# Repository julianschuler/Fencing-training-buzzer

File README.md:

# Fencing training buzzer
## Overview
This repository contains the schematic and PCB files for training buzzer circuits for sport fencing. These devices are intended to be attached directly to the plug of a foil respectively epee and will beep and flash a LED for a short period of time if a hit is detected. The buzzer circuits are powered by 1F 5.5V supercapacitors and thus can be recharged quickly by connecting them to a 5V wall adapter (less than 150 seconds for a full charge). The weapon of choice (foil or epee) can be selected via a solder jumper on the PCB.

## License
This project is licensed under the MIT license, see [`LICENSE.txt`](LICENSE.txt) for further information.

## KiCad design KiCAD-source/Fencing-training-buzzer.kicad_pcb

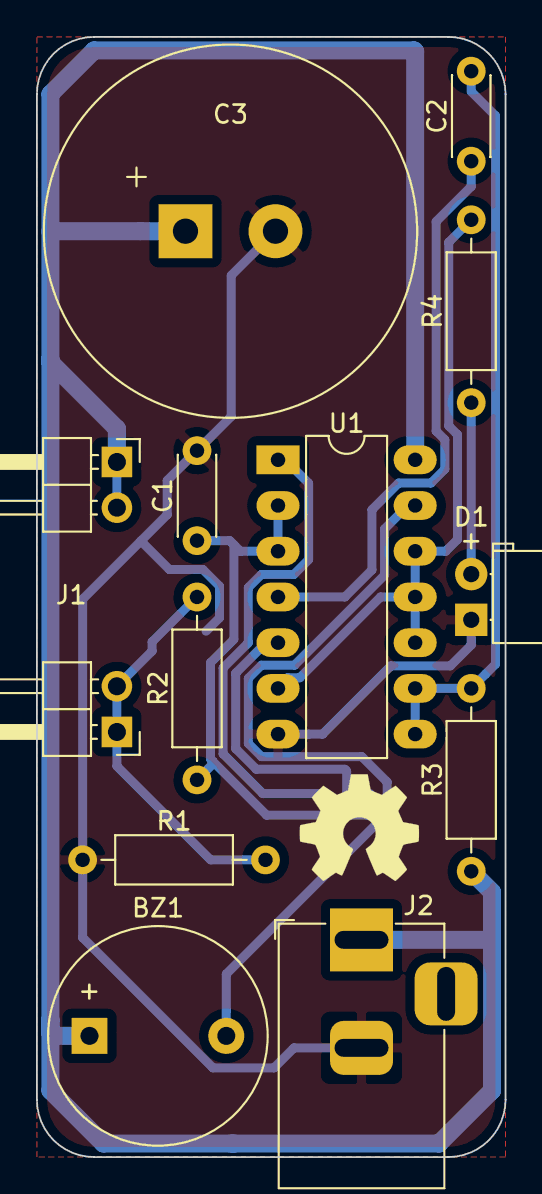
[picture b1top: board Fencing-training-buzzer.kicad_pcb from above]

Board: 2 copper layers, 26.0 x 62.2 mm, 13 parts (1 on the bottom side), 11 nets.

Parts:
BZ1: Buzzer; Buzzer_12x9.5RM7.6
C1, C2: 100nF; C_Disc_D4.3mm_W1.9mm_P5.00mm
C3: 1F; CP_Radial_Supercap_D21.5mm_P5.00mm
D1: LED; LED_D5.0mm_Horizontal_O1.27mm_Z3.0mm
J1: Con; Foil_Plug_Connector
J2: DC Jack 5V; BarrelJack_Horizontal
JP1: SolderJumper; SolderJumper-3_P1.3mm_Open_RoundedPad1.0x1.5mm
R1: 100kΩ; R_Axial_DIN0207_L6.3mm_D2.5mm_P10.16mm_Horizontal
R2: 10kΩ; R_Axial_DIN0207_L6.3mm_D2.5mm_P10.16mm_Horizontal
R3: 2.2MΩ; R_Axial_DIN0207_L6.3mm_D2.5mm_P10.16mm_Horizontal
R4: 1kΩ; R_Axial_DIN0207_L6.3mm_D2.5mm_P10.16mm_Horizontal
U1: 74HC02; DIP-14_W7.62mm_LongPads

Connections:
GND: C1.1, C3.2, D1.1, J2.2, R1.2, U1.7
unnamed: BZ1.2, U1.13
unnamed: C1.2, JP1.3, R2.2, U1.2, U1.3
unnamed: C2.1, R3.1, U1.8, U1.9
unnamed: C2.2, U1.4
unnamed: D1.2, R4.1
unnamed: J1.1, R1.1, R2.1
unnamed: JP1.1, U1.1
unnamed: JP1.2, U1.5
unnamed: R4.2, U1.6, U1.10, U1.11, U1.12
VCC: BZ1.1, C3.1, J1.2, J2.1, R3.2, U1.14

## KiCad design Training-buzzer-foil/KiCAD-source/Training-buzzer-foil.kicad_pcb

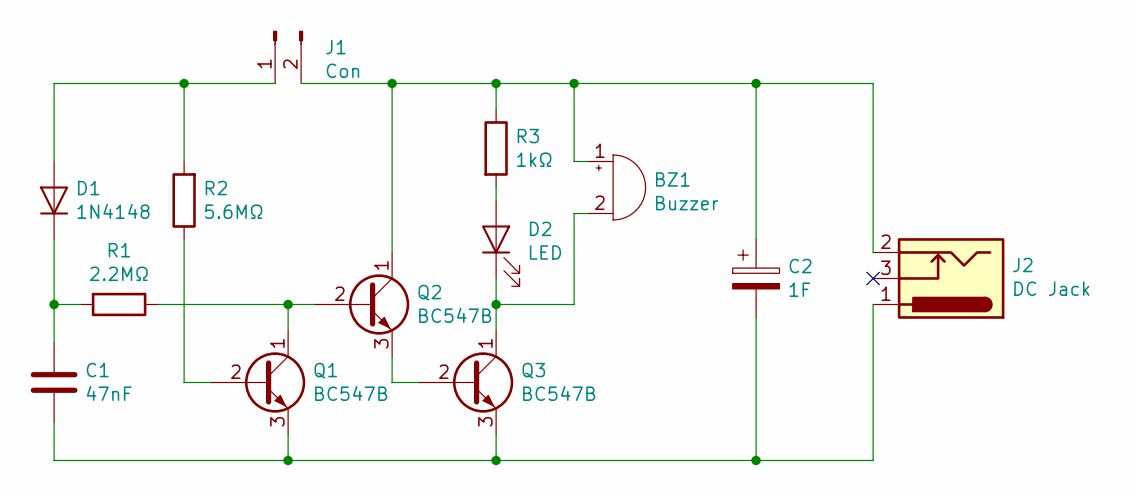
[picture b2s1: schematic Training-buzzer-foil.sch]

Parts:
BZ1: Buzzer; Buzzer_12x9.5RM7.6
C1: 47nF; C_Disc_D5.0mm_W2.5mm_P2.50mm
C2: 1F; CP_Radial_Supercap_D21.5mm_P5.00mm
D1: 1N4148; D_A-405_P7.62mm_Horizontal
D2: LED; LED_D5.0mm_Horizontal_O1.27mm_Z15.0mm
J1: Con; Foil_Plug_Connector
J2: DC Jack; BarrelJack_Horizontal
Q1, Q2, Q3: BC547B; TO-92_Inline
R1: 2.2MΩ; R_Axial_DIN0207_L6.3mm_D2.5mm_P10.16mm_Horizontal
R2: 5.6MΩ; R_Axial_DIN0207_L6.3mm_D2.5mm_P10.16mm_Horizontal
R3: 1kΩ; R_Axial_DIN0207_L6.3mm_D2.5mm_P10.16mm_Horizontal

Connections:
unnamed: BZ1.1 (-), C2.1, J1.2, J2.2, Q2.1 (C), R3.1
unnamed: BZ1.2 (+), D2.1 (K), Q3.1 (C)
unnamed: C1.1, D1.1 (K), R1.2
unnamed: C1.2, C2.2, J2.1, Q1.3 (E), Q3.3 (E)
unnamed: D1.2 (A), J1.1, R2.2
unnamed: D2.2 (A), R3.2
unnamed: Q1.1 (C), Q2.2 (B), R1.1
unnamed: Q1.2 (B), R2.1
unnamed: Q2.3 (E), Q3.2 (B)

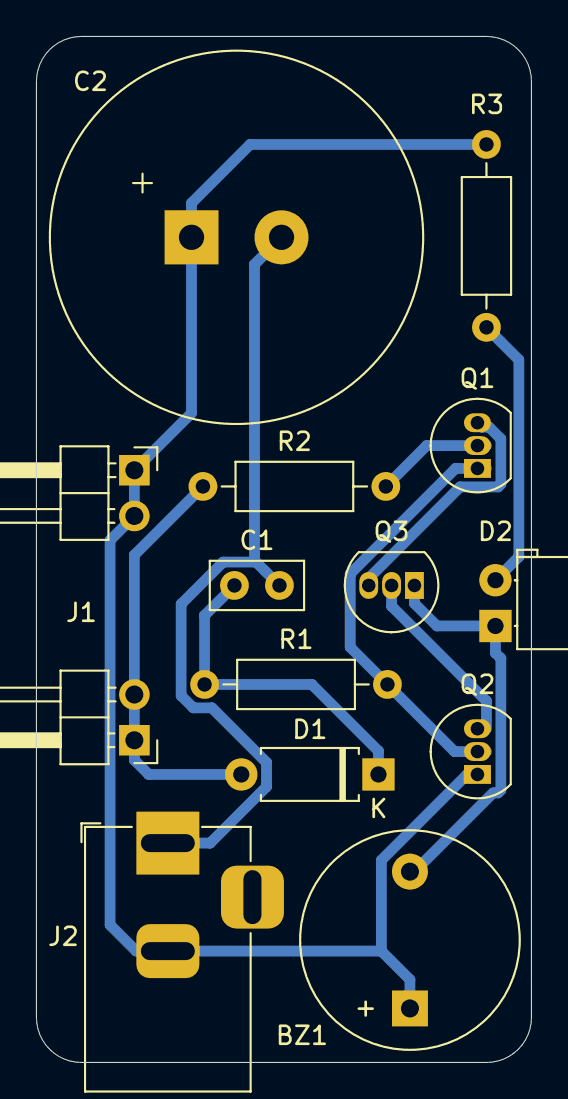
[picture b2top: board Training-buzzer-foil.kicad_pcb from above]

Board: 2 copper layers, 27.5 x 57.0 mm, 13 parts (0 on the bottom side), 9 nets.

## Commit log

2019-12-16 Add license
2019-12-17 Create PCB for foil training buzzer
2019-12-17 Add gerber files
2019-12-17 Exclude gerber files export directory
2019-12-30 Add schematic for epee training buzzer
2019-12-30 Clean up foil training buzzer schematic
2019-12-30 Add schematic for configurable training buzzer
2019-12-30 Add schematics as PDF files
2020-01-16 Update README with license information
2020-04-06 Rework circuit using NOR gates and create PCB
2020-04-06 Remove files deprecated due to the circuit rework
2020-04-06 Move and rename files for better structure
2020-04-27 Fix reverse polarity error at the barrel jack
